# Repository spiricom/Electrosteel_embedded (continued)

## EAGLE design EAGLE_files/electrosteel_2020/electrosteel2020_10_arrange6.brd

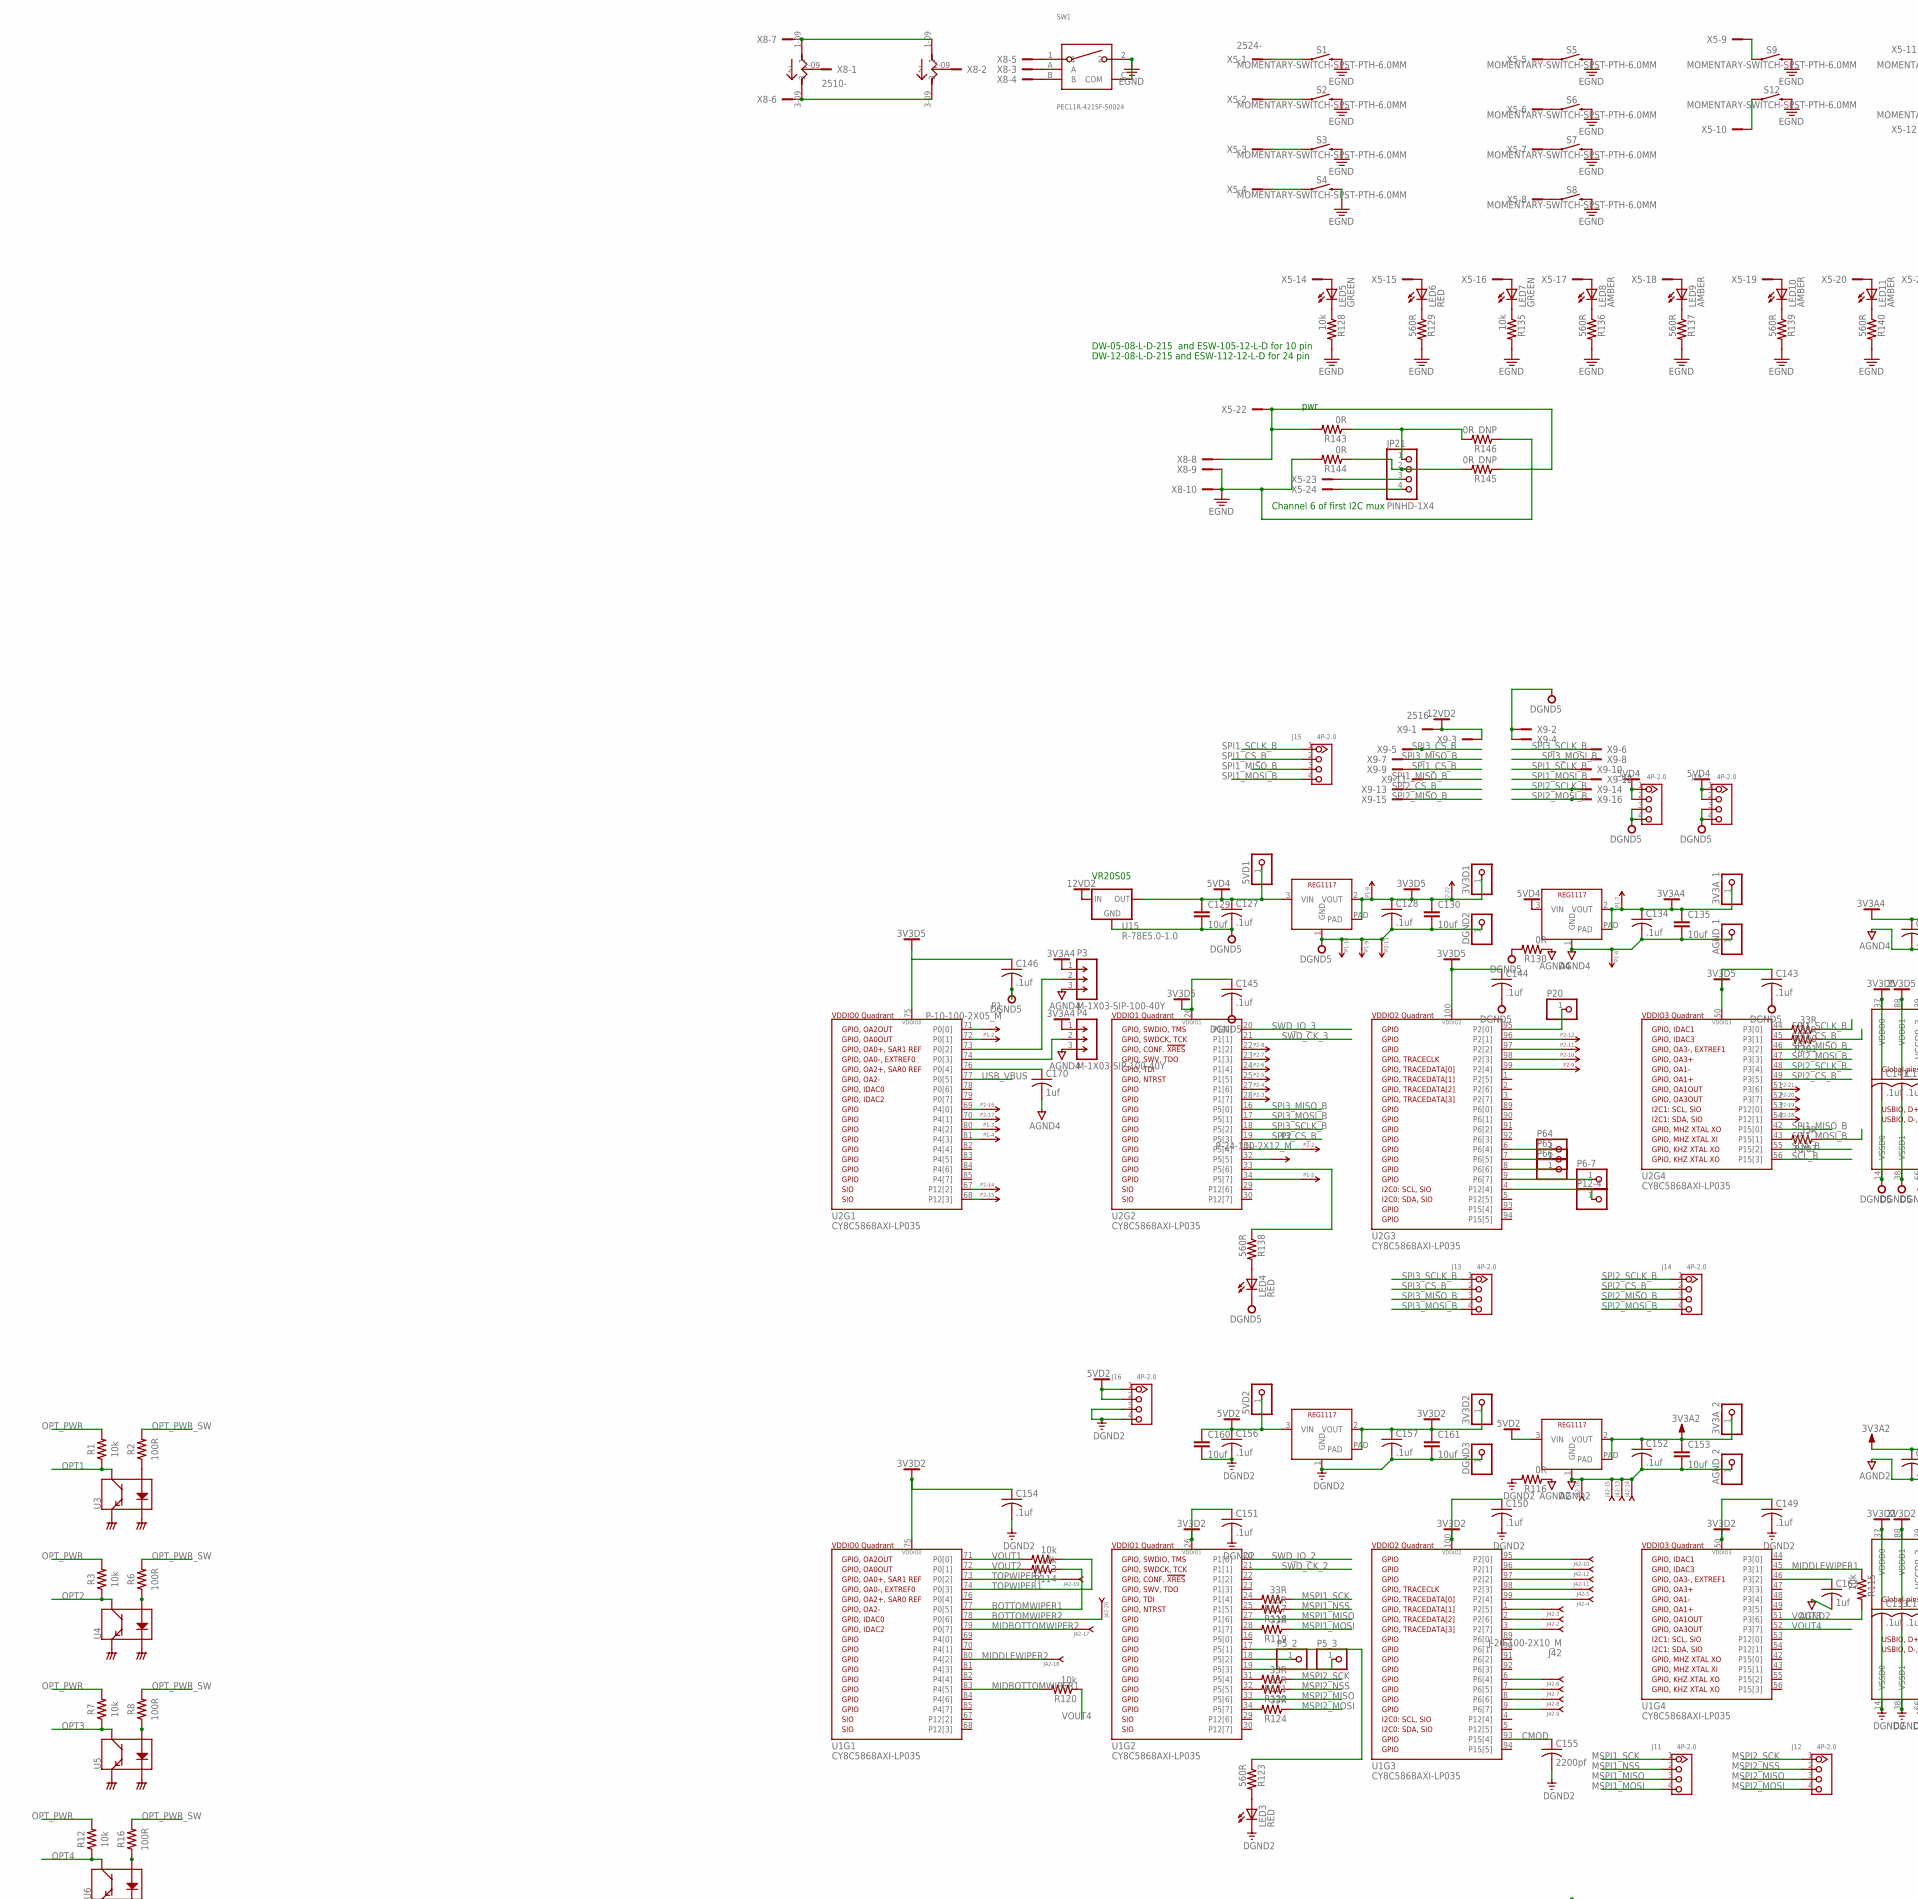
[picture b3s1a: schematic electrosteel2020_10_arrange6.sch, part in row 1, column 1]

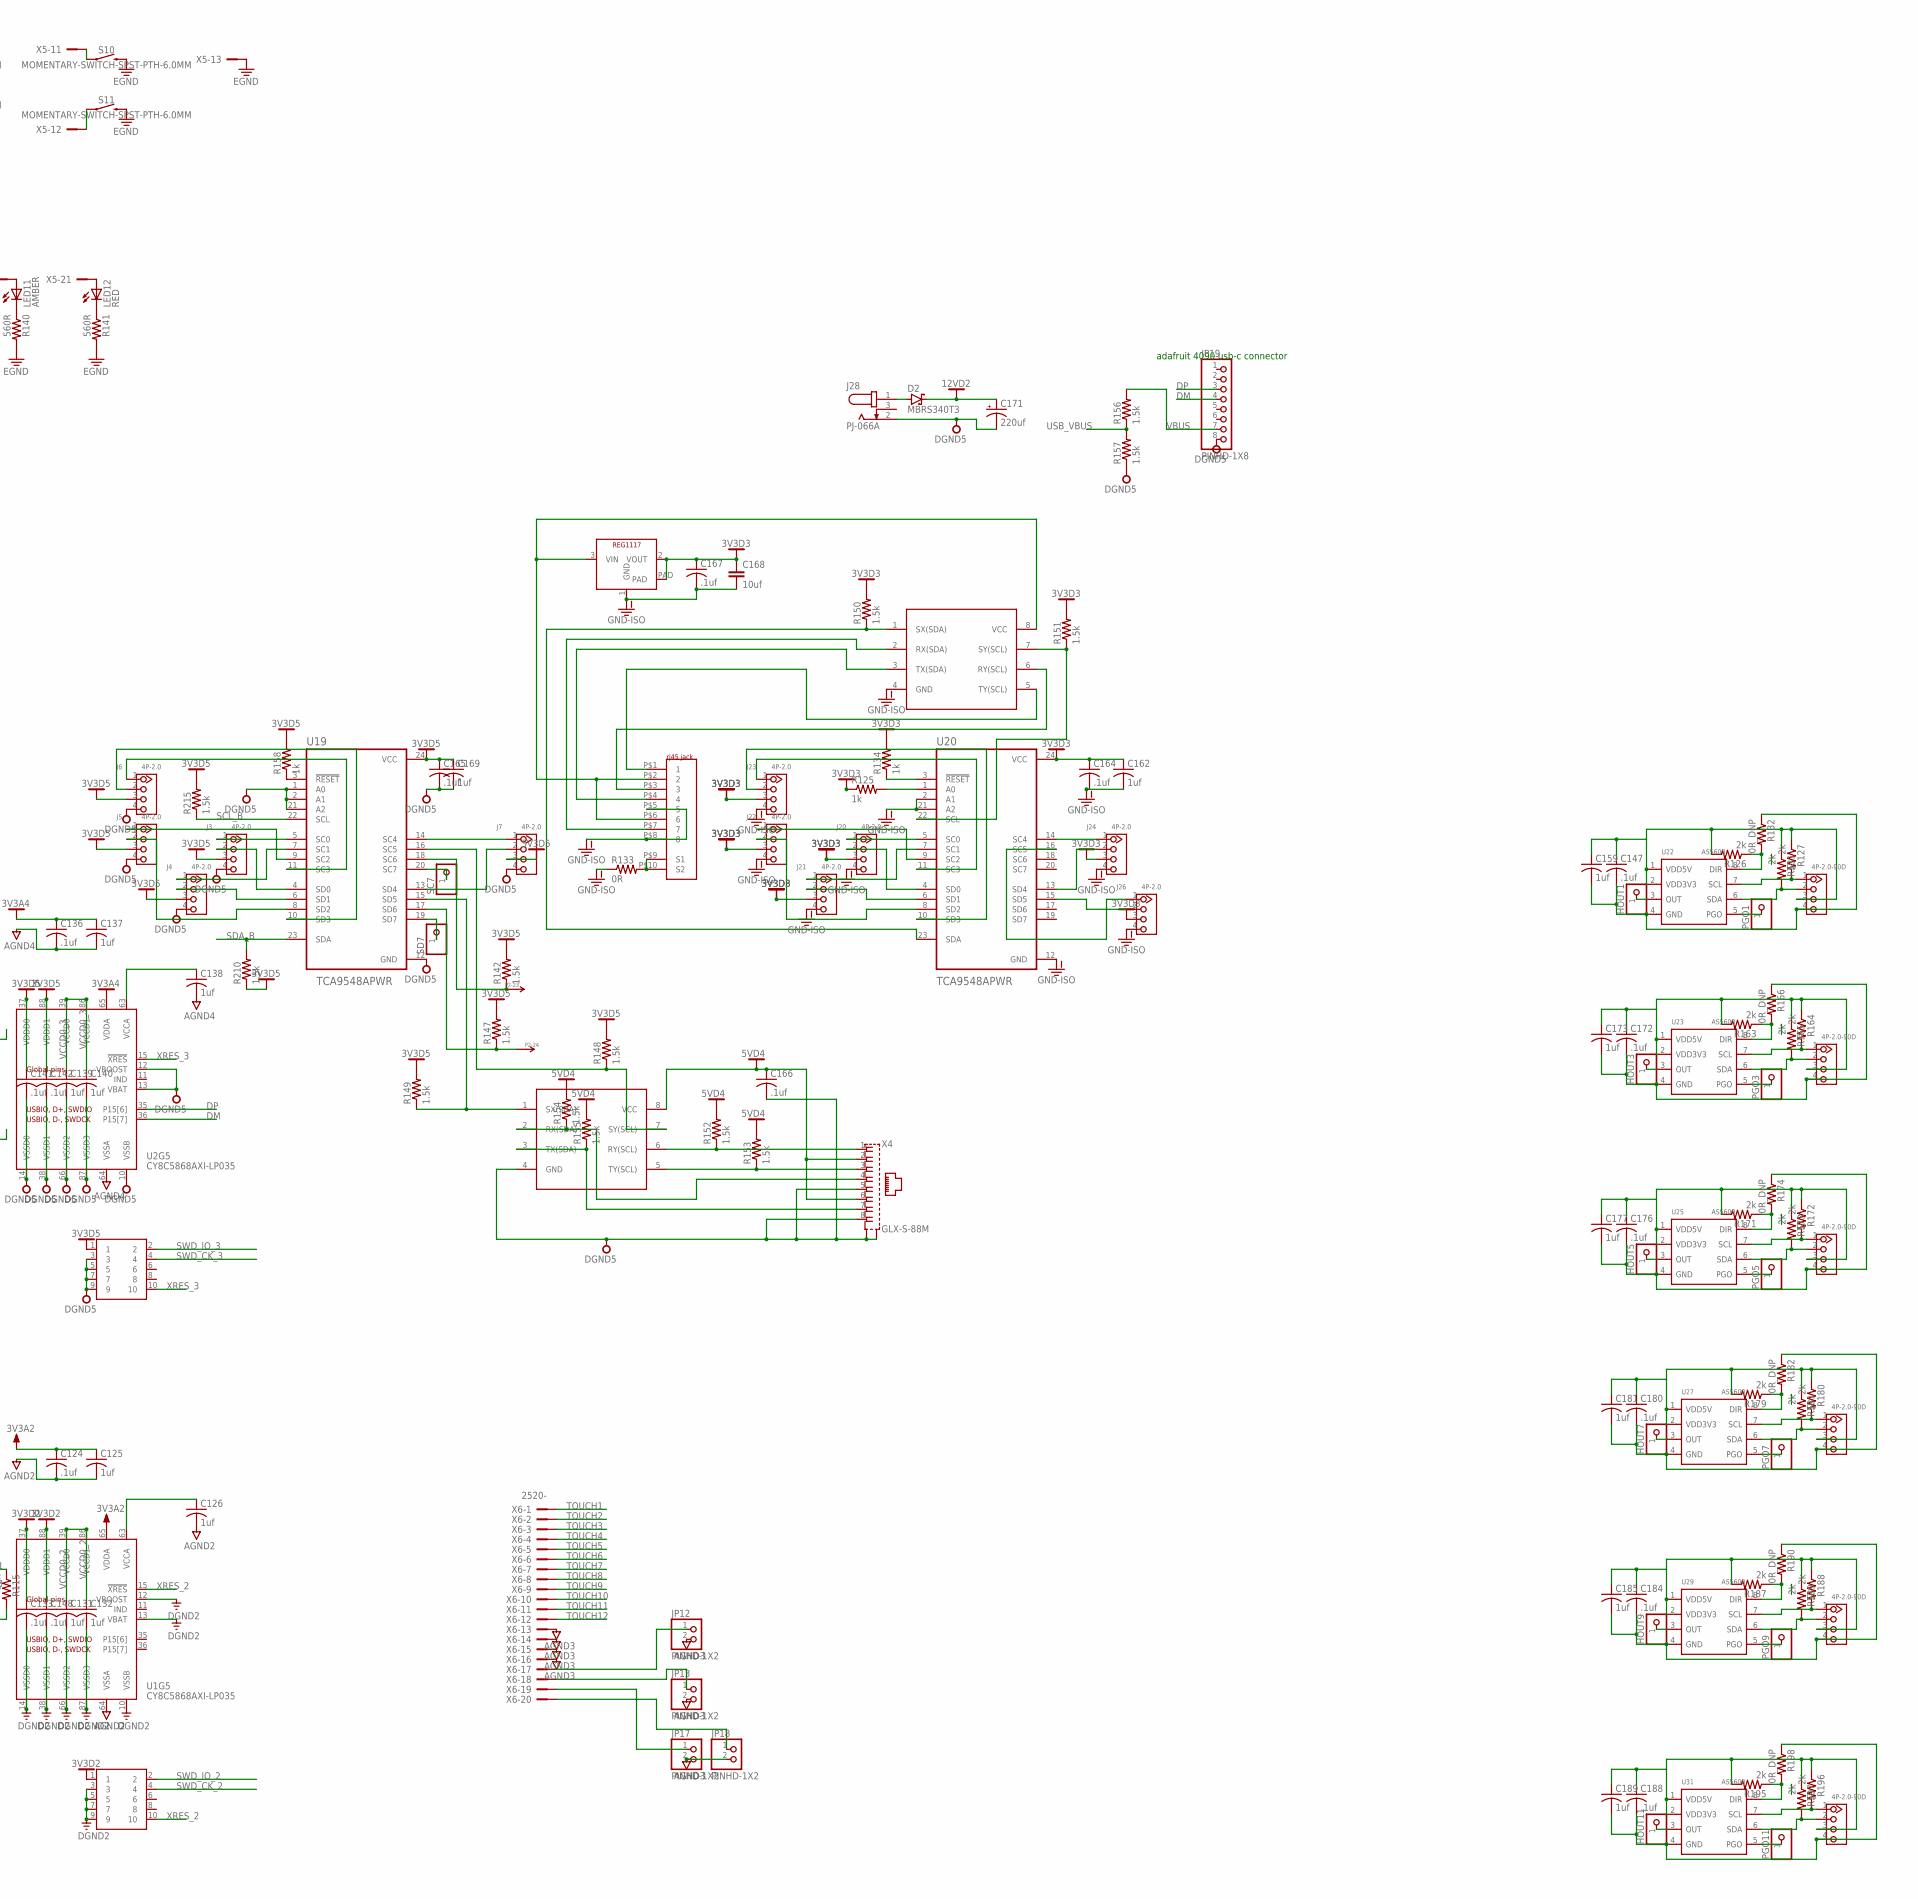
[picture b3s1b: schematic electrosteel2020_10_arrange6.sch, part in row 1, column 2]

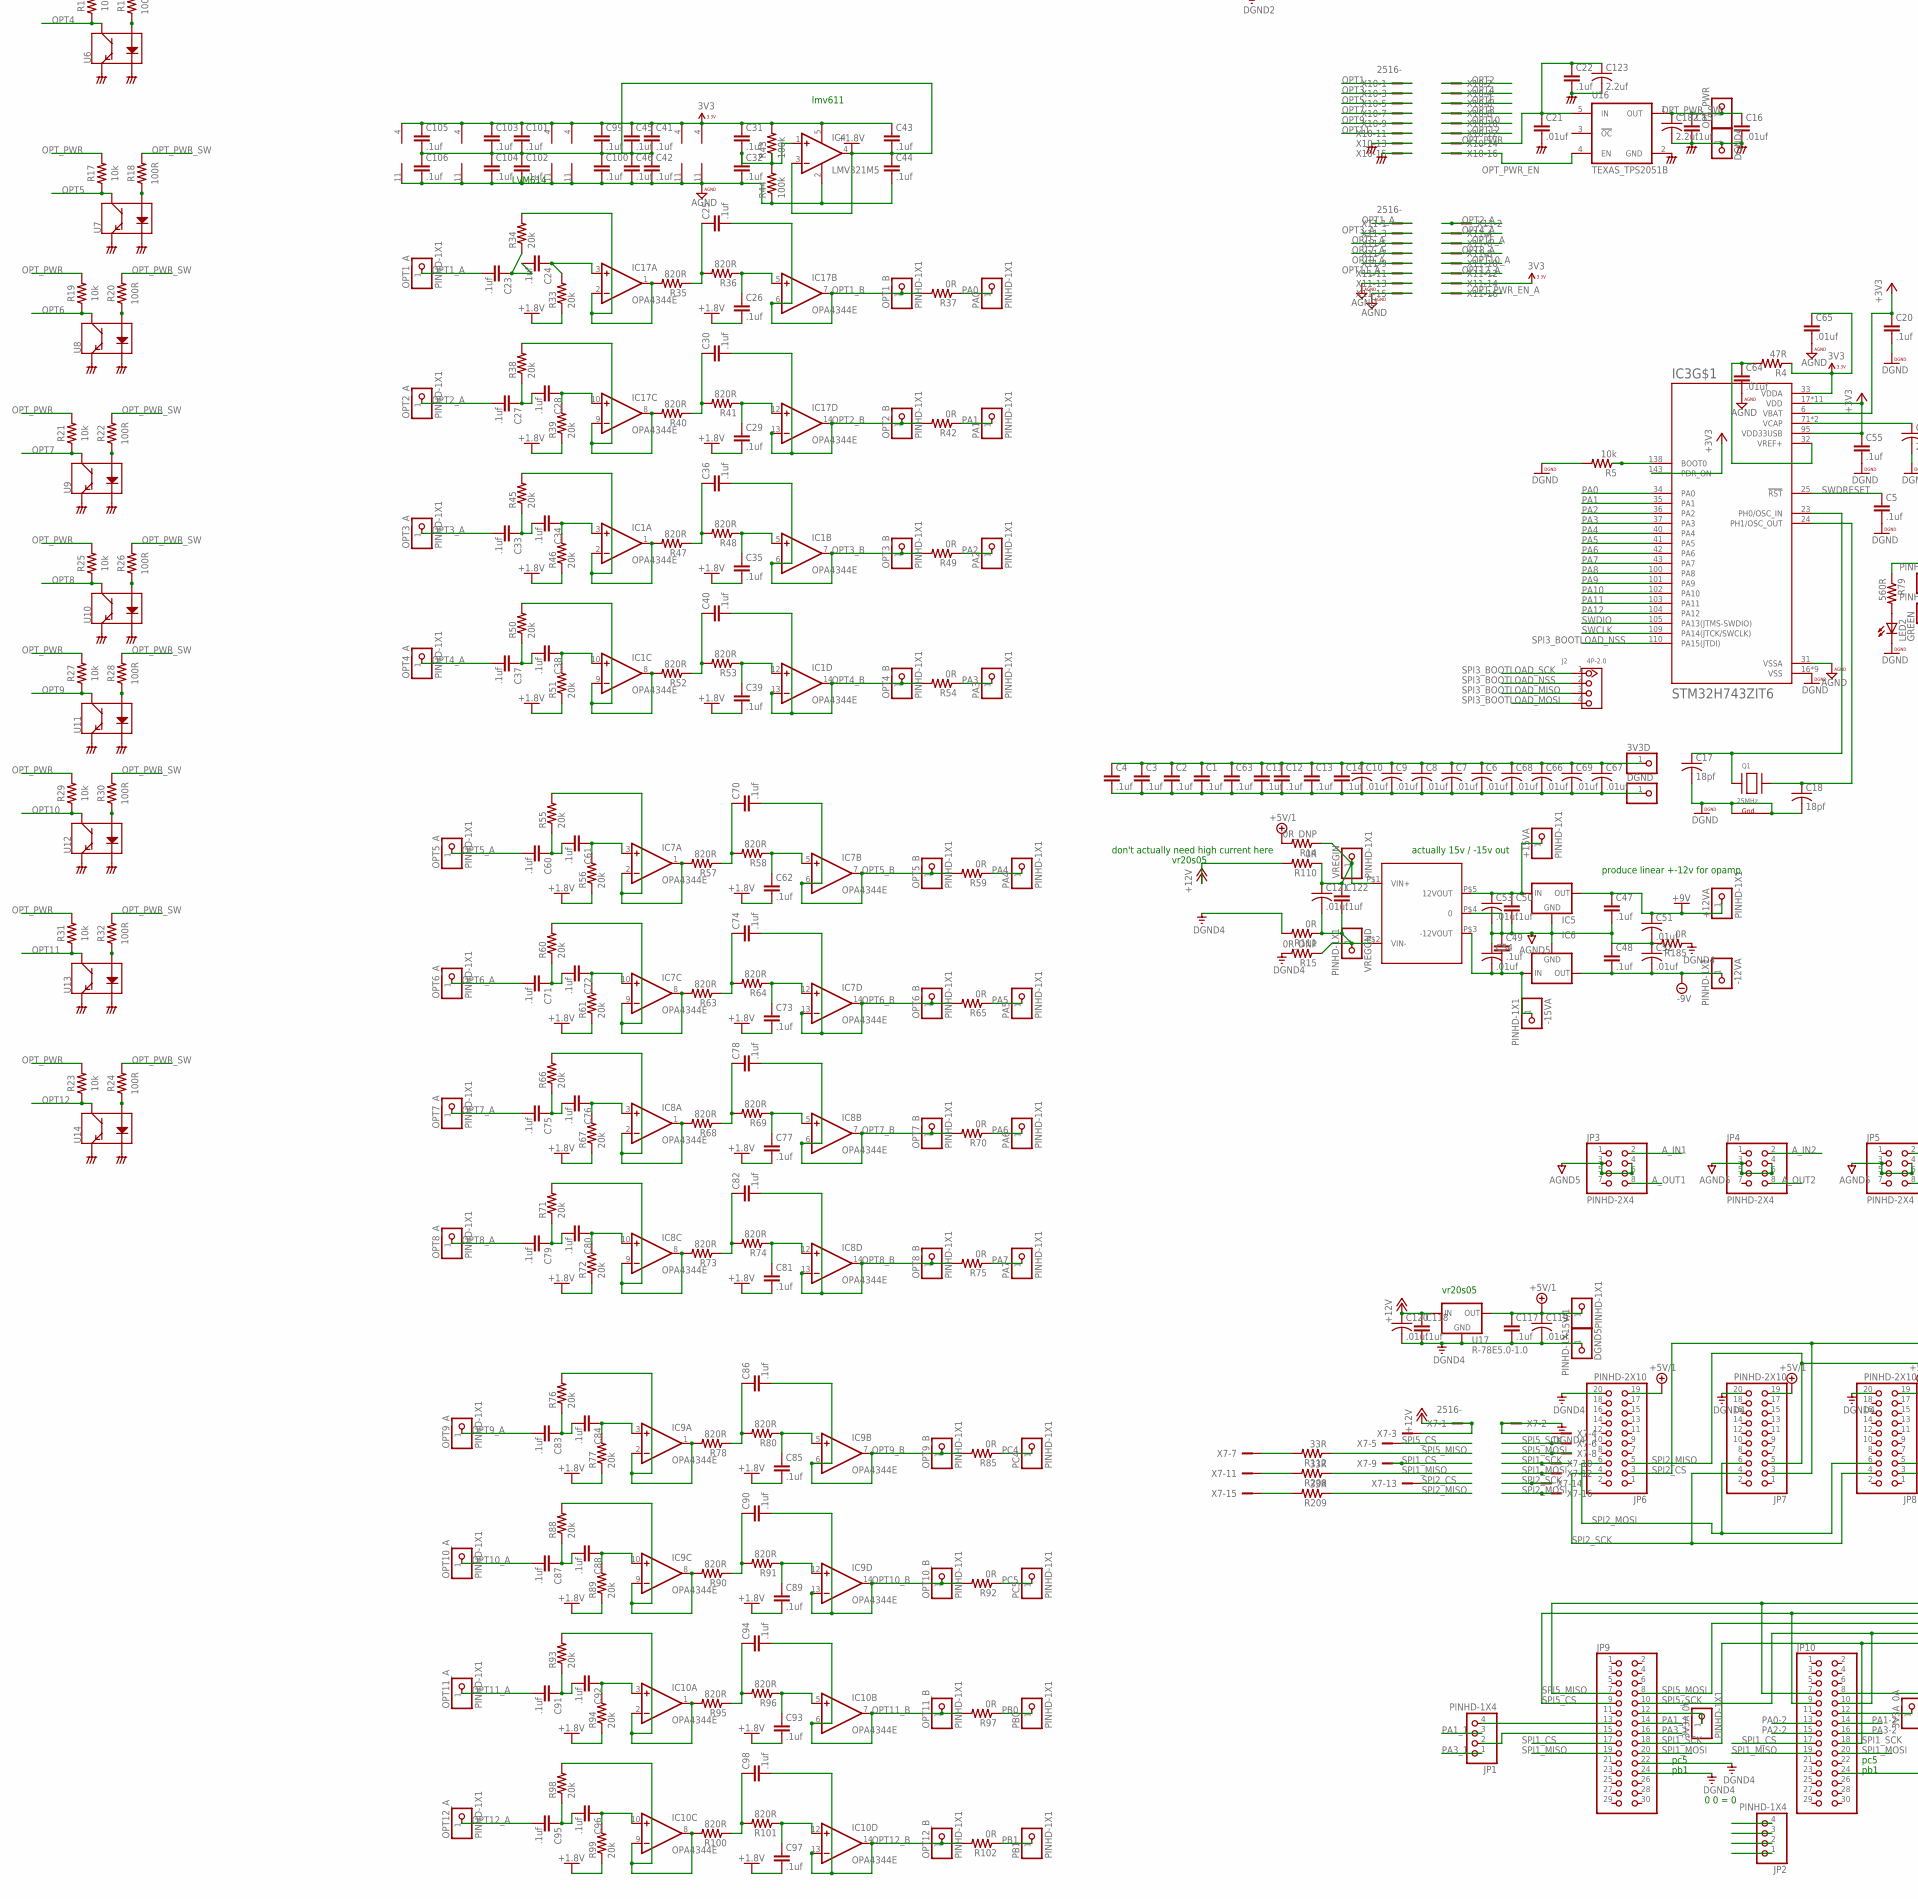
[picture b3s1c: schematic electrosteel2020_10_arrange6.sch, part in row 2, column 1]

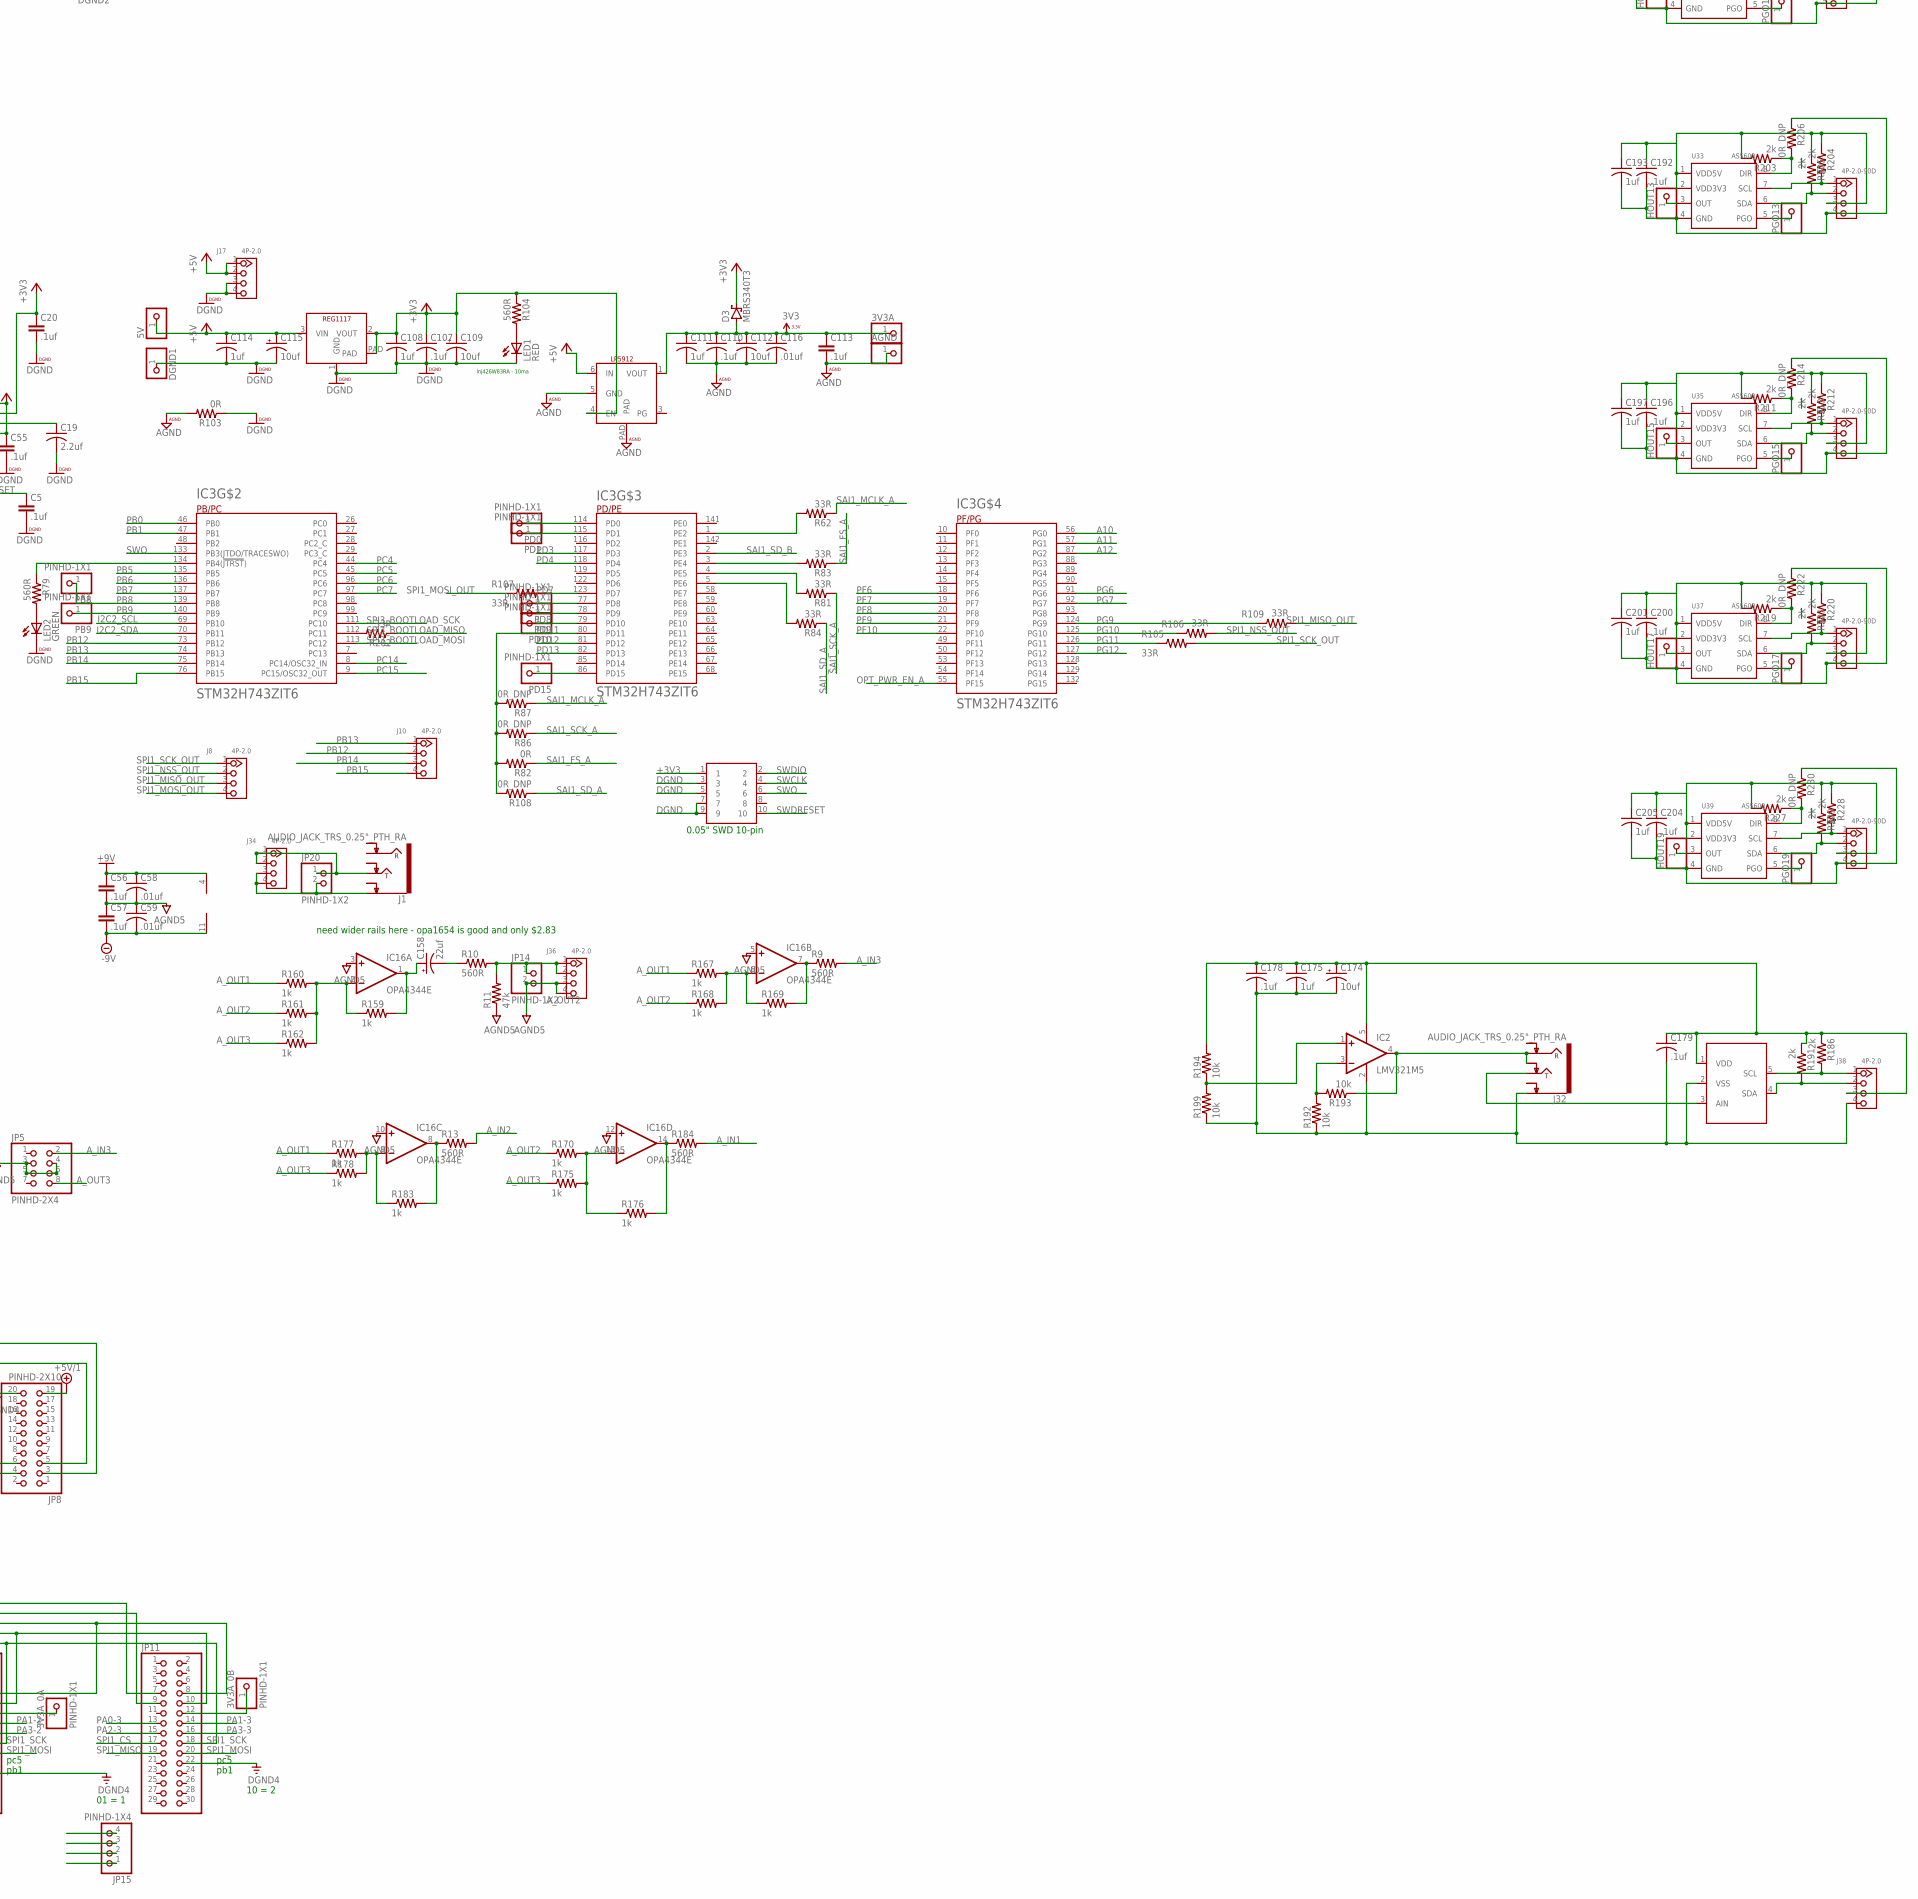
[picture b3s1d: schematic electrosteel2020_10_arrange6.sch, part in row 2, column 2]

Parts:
3V3A, 3V3A_0A, 3V3A_0B, 3V3A_0C, 3V3A_1, 3V3A_2, 3V3D, 3V3D1, 3V3D2, 5V, 5V/1, 5VD1, 5VD2: PINHD-1X1; 1X01; PARTNO *DNP
+12VA, +15VA: PINHD-1X1; 1X01; PARTNO *DNP
-12VA, -15VA: PINHD-1X1; 1X01; PARTNO *DNP
AGND: PINHD-1X1; 1X01; PARTNO *DNP
AGND_1, AGND_2: PINHD-1X1; 1X01; PARTNO *DNP
C1, C2, C3, C4, C5, C11, C12, C13, C14, C15, C20, C22, C23, C24, C25, C26, C27, C28, C29, C30, C31, C32, C33, C34, C35, C36, C37, C38, C39, C40, C41, C42, C43, C44, C45, C46, C47, C48, C49, C50, C55, C56, C57, C60, C61, C62, C63, C70, C71, C72, C73, C74, C75, C76, C77, C78, C79, C80, C81, C82, C83, C84, C85, C86, C87, C88, C89, C90, C91, C92, C93, C94, C95, C96, C97, C98, C99, C100, C101, C102, C103, C104, C105, C106, C113, C117, C118, C122: .1uf; 0402; PARTNO CC0402KRX7R8BB104
C6, C7, C8, C9, C10, C51, C52, C53, C54, C58, C59, C66, C67, C68, C69, C116, C119, C120, C121: .01uf; C0201; PARTNO TMK063B7103KP-F
C16, C21, C64, C65: .01uf; 0402; PARTNO CC0402KRX7R8BB103
C17, C18: 18pf; C0603; PARTNO CL10C180JB8NNNC
C19, C123, C182: 2.2uf; C1206; PARTNO T491A225K020AT
C107, C110, C178, C179: .1uf; C0603; PARTNO CC0603KRX7R8BB104
C108, C111, C114, C175: 1uf; C1206; PARTNO C3216X7R1E105K085AA
C109, C112, C115, C174: 10uf; SMC_B; PARTNO TAJB106K025RNJ
C124, C127, C128, C133, C134, C136, C141, C142, C143, C144, C145, C146, C147, C148, C149, C150, C151, C152, C154, C156, C157, C164, C165, C166, C167, C172, C176, C180, C184, C188, C192, C196, C200, C204: .1uf; C0603K; PARTNO CC0603KRX7R8BB104
C125, C126, C131, C132, C137, C138, C139, C140, C159, C162, C163, C169, C170, C173, C177, C181, C185, C189, C193, C197, C201, C205: 1uf; C1206K; PARTNO C3216X7R1E105K085AA
C129, C130, C135, C153, C160, C161, C168: 10uf; C1206K; PARTNO TMK316F106ZL-T
C155: 2200pf; C0603K; PARTNO C0603C222J5GACTU
C158: 22uf; PANASONIC_D; PARTNO EEE-1CA220NP
C171: 220uf; E5-10,5; PARTNO ESW227M035AH9AA
D2, D3: MBRS340T3; SMC; PARTNO MBRS340T3G
DGND, DGND1, DGND2, DGND3, DGND4, DGND5: PINHD-1X1; 1X01; PARTNO *DNP
HOUT1, HOUT3, HOUT5, HOUT7, HOUT9, HOUT11, HOUT13, HOUT15, HOUT17, HOUT19: PINHD-1X1; 1X01; PARTNO *DNP
IC1, IC7, IC8, IC9, IC10, IC17: OPA4344E; TSSOP14; PARTNO OPA4348AQPWRQ1
IC2: LMV321M5; SOT23-5; PARTNO LMV321M5
IC3: STM32H743ZIT6; QFP50P2200X2200X160-144N; PARTNO STM32H730ZBT6
IC4: LMV321M5; SOT23-5; PARTNO LMV611MF/NOPB
IC5: 78LXX; PARTNO LM78L12ACZ/LFT7
IC6: 79LXX; PARTNO L79L12ACZ-TR
IC11: LP5912; 6-WSON; PARTNO LP5912-3.3DRVT
IC12, IC13, IC14, IC15, IC18, IC20: REG1117; SOT223; PARTNO LD1117S33TR
IC16: OPA4344E; TSSOP14; PARTNO OPA1654AIPWR
J1, J32: AUDIO_JACK_TRS_0.25"_PTH_RA; AUDIO_JACK_0.25"_TRS_PTH_RA; PARTNO NRJ6HM-1
J2, J3, J4, J5, J6, J7, J8, J10, J11, J12, J13, J14, J15, J16, J17, J18, J19, J20, J21, J22, J23, J24, J26, J34, J36, J38: 4P-2.0; HW4-2.0; PARTNO 110990030
J9, J25, J27, J29, J31, J33, J35, J37, J39, J41: 4P-2.0-90D; HW4-2.0-90D; PARTNO 110990037
J28: PJ-066A; CUI_PJ-066A; PARTNO PJ-066A
J42: J-20-100-2X10_M; DIL-100-2X10_M; PARTNO RS2-20-G
JP1, JP2, JP15: PINHD-1X4; 1X04
JP3, JP4, JP5: PINHD-2X4; 2X04; PARTNO 77313-101-08LF
JP6, JP7, JP8: PINHD-2X10; 2X10; PARTNO 77313-101-20LF
JP9, JP10, JP11: PINHD-2X15; 2X15; PARTNO 77313-101-30LF
JP12, JP13, JP14, JP17, JP18, JP20: PINHD-1X2; 1X02; PARTNO *DNP
JP19: PINHD-1X8; 1X08; PARTNO *DNP
JP21: PINHD-1X4; 1X04; PARTNO *DNP
LED1, LED3, LED4: RED; CHIP-LED0603; PARTNO 5973006507F
LED2: GREEN; CHIP-LED0603; PARTNO 5973506507F
LED5, LED7: GREEN; P-LCC-2; PARTNO HSMM-A101-R00J1
LED6, LED12: RED; P-LCC-2; PARTNO HSMZ-A100-R00J1
LED8, LED9, LED10, LED11: AMBER; P-LCC-2; PARTNO HSMU-A100-S00J1
OPT1_A, OPT1_B, OPT2_A, OPT2_B, OPT3_A, OPT3_B, OPT4_A, OPT4_B, OPT5_A, OPT5_B, OPT6_A, OPT6_B, OPT7_A, OPT7_B, OPT8_A, OPT8_B, OPT9_A, OPT9_B, OPT10_A, OPT10_B, OPT11_A, OPT11_B, OPT12_A, OPT12_B: PINHD-1X1; 1X01; PARTNO *DNP
OPT_PWR: PINHD-1X1; 1X01; PARTNO *DNP
P1: P-10-100-2X05_M; DIL-100-2X05_M; PARTNO ESW-105-12-L-D
P2: P-24-100-2X12_M; DIL-100-2X12_M; PARTNO ESW-112-12-L-D
P3, P4: M-1X03-SIP-100-40Y; SIP-100-03-40Y; PARTNO *DNP
P5_2, P5_3, P6-7, P12-4, P20, P64, P65, P66: PINHD-1X1; 1X01; PARTNO *DNP
PA0, PA1, PA2, PA3, PA4, PA5, PA6, PA7: PINHD-1X1; 1X01; PARTNO *DNP
PB0, PB1, PB8, PB9: PINHD-1X1; 1X01; PARTNO *DNP
PC4, PC5: PINHD-1X1; 1X01; PARTNO *DNP
PD0, PD1, PD8, PD9, PD10, PD15: PINHD-1X1; 1X01; PARTNO *DNP
PGO1, PGO3, PGO5, PGO7, PGO9, PGO11, PGO13, PGO15, PGO17, PGO19: PINHD-1X1; 1X01; PARTNO *DNP
Q1: 25MHz; NX3225; PARTNO 7M-25.000MAAJ-T
R1, R3, R7, R12, R17, R19, R21, R23, R25, R27, R29, R31: 10k; RESC1608X60; PARTNO ESR03EZPF1002
R2, R6, R8, R16, R18, R20, R22, R24, R26, R28, R30, R32: 100R; RESC1608X60; PARTNO ESR03EZPJ101
R4: 47R; R0603; PARTNO ESR03EZPJ470
R5: 10k; R0603; PARTNO RC0402FR-0710KL
R9, R10, R13, R79, R104, R123, R129, R136, R137, R138, R139, R140, R141, R184: 560R; R0603; PARTNO ESR03EZPF5600
R11: 47k; R0603; PARTNO ESR03EZPJ473
R14, R15, R86, R87, R108, R132, R145, R146, R166, R174, R182, R190, R198, R206, R214, R222, R230: 0R_DNP; R0603; PARTNO *DNP
R33, R34, R38, R39, R45, R46, R50, R51, R55, R56, R60, R61, R66, R67, R71, R72, R76, R77, R88, R89, R93, R94, R98, R99: 20k; R0603; PARTNO ESR03EZPF2002
R35, R36, R40, R41, R47, R48, R52, R53, R57, R58, R63, R64, R68, R69, R73, R74, R78, R80, R90, R91, R95, R96, R100, R101: 820R; R0603; PARTNO RCS0603820RFKEA
R37, R42, R49, R54, R59, R65, R70, R75, R85, R92, R97, R102, R133: 0R; R0603; PARTNO RC0603JR-070RL
R43, R44: 100k; R0603; PARTNO ESR03EZPF1003
R62, R81, R83, R84, R112, R117, R118, R119, R121, R122, R124, R200, R201, R202, R207, R208, R209: 33R; R0201; PARTNO RC0201FR-0733RL
R82, R103, R110, R111, R185: 0R; R0603; PARTNO RCS06030000Z0EA
R105, R106, R107, R109: 33R; 0402; PARTNO RC0402FR-0733RL
R113, R114, R115, R120, R192, R193, R194, R199: 10k; R0603; PARTNO ESR03EZPF1002
R116, R130, R143, R144: 0R; R0603; PARTNO CRCW06030000Z0EAHP
R125, R134, R158, R159, R160, R161, R162, R167, R168, R169, R170, R175, R176, R177, R178, R183: 1k; R0603; PARTNO ESR03EZPF1001
R126, R127, R131, R163, R164, R165, R171, R172, R173, R179, R180, R181, R186, R187, R188, R189, R191, R195, R196, R197, R203, R204, R205, R211, R212, R213, R219, R220, R221, R227, R228, R229: 2k; R0603; PARTNO ERJ-PA3F2001V
R128, R135: 10k; R0603; PARTNO ESR03EZPF5600
R142, R147, R148, R149, R150, R151, R152, R153, R154, R155, R156, R157, R210, R215: 1.5k; R0603; PARTNO ESR03EZPJ152
S1, S2, S3, S4, S5, S6, S7, S8, S9, S10, S11, S12: MOMENTARY-SWITCH-SPST-PTH-6.0MM; TACTILE_SWITCH_PTH_6.0MM; PARTNO TL1105SPF160Q
SC7: PINHD-1X1; 1X01; PARTNO *DNP
SD7: PINHD-1X1; 1X01; PARTNO *DNP
SW1: PEC11R-4215F-S0024; PARTNO PEC11R-4215F-S0024
U1: CY8C5868AXI-LP035; TQFP-100-14X14MM; PARTNO CY8C5888AXI-LP096
U2: CY8C5868AXI-LP035; TQFP-100-14X14MM; PARTNO CY8C5468AXI-LP042
U3, U4, U5, U6, U7, U8, U9, U10, U11, U12, U13, U14: QRE1113; PARTNO QRE1113GR
U15, U17: R-78E5.0-1.0; DC-DC_CONVERTER_78XX; PARTNO R-78E5.0-1.0
U16: TEXAS_TPS2051B; TEXAS_SOT23-5; PARTNO TPS2051BDBVRG4
U19, U20: TCA9548APWR; SOP65P640X120-24N; PARTNO TCA9548APWR
U22, U23, U25, U27, U29, U31, U33, U35, U37, U39: AS5600; SOIC8-1.27-5X4MM; PARTNO AS5600-ASOM
U$1, U$2: RK09; PARTNO RK09L1220A1B
U$3: CMR0512S3C; PARTNO DPU01M-15
U$5: MCP3221; SOT23-5L; PARTNO MCP3221A7T-E/OT
U$6: SS-7188VS-A-FLS; SS-7188VS-A-FLS_RJ45; PARTNO SS-7188VS-A-FLS
U$9, U$10: P82B96DP,118; SO8; PARTNO P82B96TD*112
VREGGND: PINHD-1X1; 1X01; PARTNO *DNP
VREGIN: PINHD-1X1; 1X01; PARTNO *DNP
X1, X2, X3: 3221-10-0300-00; PARTNO 4048
X4: GLX-S-88M; PARTNO GLX-S-88M
X5: 2524-; PAK100/2500-24; PARTNO DW-12-08-L-D-215
X6: 2520-; PAK100/2500-20; PARTNO N2520-6003-UG
X7, X9, X10, X11: 2516-; PAK100/2500-16; PARTNO D2516-6002-AR
X8: 2510-; PAK100/2500-10; PARTNO DW-05-08-L-D-215

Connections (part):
3V3: C31.1, C41.1, C43.1, C45.1, C99.1, C101.1, C103.1, C105.1, IC1.4 (V+), IC4.5 (V+), IC7.4 (V+), IC8.4 (V+), IC9.4 (V+), IC10.4 (V+), IC17.4 (V+), R43.2, X11.14
3V3A: 3V3A.1, C65.1, C110.1, C111.1, C112.+, C113.1, C116.1, D3.A, IC3.33 (VDDA), IC11.1 (VOUT), R4.1
3V3A2: 3V3A_2.1, C124.1, C125.1, C152.1, C153.1, IC18.2 (VOUT), IC18.PAD, U1.65 (VDDA)
3V3A4: 3V3A_1.1, C134.1, C135.1, C136.1, C137.1, IC14.2 (VOUT), IC14.PAD, P1.7, P3.1, P4.1, U2.65 (VDDA)
3V3D2: 3V3D2.1, C133.1, C148.1, C149.1, C150.1, C151.1, C154.1, C157.1, C161.1, IC20.2 (VOUT), IC20.PAD, U1.26 (VDDIO1), U1.37 (VDDD0), U1.50 (VDDIO3), U1.75 (VDDIO0), U1.88 (VDDD1), U1.100 (VDDIO2), X3.1
3V3D3: C162.1, C164.1, C167.1, C168.1, IC15.2 (VOUT), IC15.PAD, J20.3, J21.3, J22.3, J23.3, J24.3, J26.3, R125.1, R134.2, R150.2, R151.2, U20.24 (VCC)
3V3D5: 3V3D1.1, C128.1, C130.1, C141.1, C142.1, C143.1, C144.1, C145.1, C146.1, C165.1, C169.1, IC13.2 (VOUT), IC13.PAD, J3.3, J4.3, J5.3, J6.3, J7.3, P1.8, P2.22, R142.2, R147.2, R148.2, R149.2, R158.2, R210.1, R215.2, U2.26 (VDDIO1), U2.37 (VDDD0), U2.50 (VDDIO3), U2.75 (VDDIO0), U2.88 (VDDD1), U2.100 (VDDIO2), U19.24 (VCC), X1.1
5VD2: 5VD2.1, C156.1, C160.1, IC18.3 (VIN), IC20.3 (VIN), J16.1, J16.2
5VD4: 5VD1.1, C127.1, C129.1, C166.1, IC13.3 (VIN), IC14.3 (VIN), J18.1, J18.2, J19.1, J19.2, R152.2, R153.2, R154.2, R155.2, U15.VOUT (OUT), U$9.8 (VCC), X4.2, X4.6
12VD2: C171.+, D2.C, U15.VIN (IN), X9.1, X9.3
+1.8V: C26.2, C29.2, C35.2, C39.2, C41.2, C42.1, C43.2, C44.1, C45.2, C46.1, C62.2, C73.2, C77.2, C81.2, C85.2, C89.2, C93.2, C97.2, C99.2, C100.1, C101.2, C102.1, C103.2, C104.1, C105.2, C106.1, IC4.3 (-IN), IC4.4 (OUT), R33.1, R39.1, R46.1, R51.1, R56.1, R61.1, R67.1, R72.1, R77.1, R89.1, R94.1, R99.1
+3V3: 3V3D.1, C1.1, C2.1, C3.1, C4.1, C6.1, C7.1, C8.1, C9.1, C10.1, C11.1, C12.1, C13.1, C14.1, C20.1, C55.1, C63.1, C66.1, C67.1, C68.1, C69.1, C107.1, C108.1, C109.+, D3.C, IC3.6 (VBAT), IC3.17 (VDD), IC3.30 (VDD), IC3.39 (VDD), IC3.52 (VDD), IC3.62 (VDD), IC3.72 (VDD), IC3.84 (VDD), IC3.95 (VDD33USB), IC3.108 (VDD), IC3.121 (VDD), IC3.131 (VDD), IC3.143 (PDR_ON), IC3.144 (VDD), IC11.4 (EN), IC12.2 (VOUT), IC12.PAD, R104.1, X2.1
+5V: 5V.1, C114.1, C115.+, IC11.6 (IN), IC12.3 (VIN), J17.1, J17.2
+5V/1: 5V/1.1, C117.1, C119.1, JP6.19, JP7.19, JP8.19, R14.2, U17.VOUT (OUT)
+9V: +12VA.1, C47.1, C51.1, C56.1, C58.1, IC5.OUT, IC16.4 (V+)
+12V: C118.1, C120.1, R110.2, U17.VIN (IN), X7.1, X7.3
-9V: -12VA.1, C48.2, C52.2, C57.2, C59.2, IC6.OUT, IC16.11 (V-)
A10: IC3.56 (PG0)
A11: IC3.57 (PG1)
A12: IC3.87 (PG2)
AGND: AGND.1, C32.2, C42.2, C44.2, C46.2, C64.2, C65.2, C100.2, C102.2, C104.2, C106.2, C110.2, C111.2, C112.-, C113.2, C116.2, IC1.11 (V-), IC3.31 (VSSA), IC4.2 (V-), IC7.11 (V-), IC8.11 (V-), IC9.11 (V-), IC10.11 (V-), IC11.5 (GND), IC11.PAD, IC17.11 (V-), R44.1, R103.2, X11.13, X11.15
AGND2: AGND_2.1, C124.2, C125.2, C126.2, C152.2, C153.2, C163.2, IC18.1 (GND), J42.13, J42.14, J42.15, J42.16, R116.1, U1.64 (VSSA)
AGND3: JP12.2, JP13.2, JP17.2, JP18.2, X6.13, X6.14, X6.15, X6.16
AGND4: AGND_1.1, C134.2, C135.2, C136.2, C137.2, C138.2, C170.2, IC14.1 (GND), P1.6, P3.3, P4.3, R130.1, U2.64 (VSSA)
AGND5: C47.2, C48.1, C49.1, C50.2, C51.2, C52.1, C53.2, C54.1, C56.2, C57.1, C58.2, C59.1, IC5.GND, IC6.GND, IC16.3 (+IN), IC16.5 (+IN), IC16.10 (+IN), IC16.12 (+IN), J36.3, J36.4, JP3.3, JP3.4, JP3.5, JP3.6, JP4.3, JP4.4, JP4.5, JP4.6, JP5.3, JP5.4, JP5.5, JP5.6, JP14.2, R11.1, R185.2, U$3.P$4 (0)
A_IN1: JP3.2, R184.2
A_IN2: JP4.2, R13.2
A_IN3: JP5.2, R9.2
A_OUT1: JP3.8, R160.1, R167.1, R177.1
A_OUT2: JP4.8, R161.1, R168.1, R170.1
A_OUT3: JP5.8, R162.1, R175.1, R178.1
BOTTOMWIPER1: R114.1, U1.77 (P0[5])
BOTTOMWIPER2: J42.20, U1.78 (P0[6])
CGND: C15.2, C16.2, C21.2, C22.2, C123.2, C182.2, DGND4.1, U3.2 (K), U3.4 (E), U4.2 (K), U4.4 (E), U5.2 (K), U5.4 (E), U6.2 (K), U6.4 (E), U7.2 (K), U7.4 (E), U8.2 (K), U8.4 (E), U9.2 (K), U9.4 (E), U10.2 (K), U10.4 (E), U11.2 (K), U11.4 (E), U12.2 (K), U12.4 (E), U13.2 (K), U13.4 (E), U14.2 (K), U14.4 (E), U16.2 (GND), X10.13, X10.15
CMOD: C155.1, U1.93 (P15[4])
DGND: C1.2, C2.2, C3.2, C4.2, C5.2, C6.2, C7.2, C8.2, C9.2, C10.2, C11.2, C12.2, C13.2, C14.2, C17.2, C18.2, C19.2, C20.2, C55.2, C63.2, C66.2, C67.2, C68.2, C69.2, C107.2, C108.2, C109.-, C114.2, C115.-, DGND.1, DGND1.1, IC3.16 (VSS), IC3.38 (VSS), IC3.51 (VSS), IC3.61 (VSS), IC3.83 (VSS), IC3.94 (VSS), IC3.107 (VSS), IC3.120 (VSS), IC3.130 (VSS), IC12.1 (GND), J17.3, J17.4, LED1.C, LED2.C, Q1.2 (G2), Q1.4 (G1), R5.2, R103.1, X2.3, X2.5, X2.7, X2.9
DGND2: C131.2, C132.2, C133.2, C148.2, C149.2, C150.2, C151.2, C154.2, C155.2, C156.2, C157.2, C160.2, C161.2, DGND3.1, IC20.1 (GND), J16.3, J16.4, LED3.C, R116.2, U1.10 (VSSB), U1.12 (VBOOST), U1.13 (VBAT), U1.14 (VSSD0), U1.38 (VSSD1), U1.66 (VSSD2), U1.87 (VSSD3), X3.3, X3.5, X3.7, X3.9
DGND4: C117.2, C118.2, C119.2, C120.2, DGND5.1, JP6.20, JP7.20, JP8.20, JP9.22, JP9.24, JP10.24, JP11.22, R15.2, R111.2, R185.1, U17.GND, X7.2, X7.4
DGND5: C127.2, C128.2, C129.2, C130.2, C139.2, C140.2, C141.2, C142.2, C143.2, C144.2, C145.2, C146.2, C165.2, C166.2, C169.2, C171.-, DGND2.1, IC13.1 (GND), J3.4, J4.4, J5.4, J6.4, J7.4, J18.3, J18.4, J19.3, J19.4, J28.2, JP19.8, LED4.C, P1.9, P1.10, P2.13, R130.2, R157.1, U2.10 (VSSB), U2.12 (VBOOST), U2.13 (VBAT), U2.14 (VSSD0), U2.38 (VSSD1), U2.66 (VSSD2), U2.87 (VSSD3), U15.GND, U19.1 (A0), U19.2 (A1), U19.12 (GND), U19.21 (A2), U$9.4 (GND), X1.3, X1.5, X1.7, X1.9, X4.5, X4.8, X4.S1, X4.S2, X9.2, X9.4
DM: JP19.4, U2.36 (P15[7])
DP: JP19.3, U2.35 (P15[6])
EGND: R128.2, R129.2, R135.2, R136.2, R137.2, R139.2, R140.2, R141.2, R144.2, R146.1, S1.3 (2), S2.3 (2), S3.3 (2), S4.3 (2), S5.3 (2), S6.3 (2), S7.3 (2), S8.3 (2), S9.3 (2), S10.3 (2), S11.3 (2), S12.3 (2), SW1.2, SW1.C (COM), X5.13, X8.9, X8.10
GND-ISO: C162.2, C164.2, C167.2, C168.2, IC15.1 (GND), J20.4, J21.4, J22.4, J23.4, J24.4, J26.4, R133.1, U20.2 (A1), U20.12 (GND), U20.21 (A2), U$6.P$5 (5), U$6.P$8 (8), U$10.4 (GND)
I2C2_SCL: IC3.69 (PB10)
I2C2_SDA: IC3.70 (PB11)
MIDBOTTOMWIPER1: R120.2, U1.83 (P4[5])
MIDBOTTOMWIPER2: J42.17, U1.79 (P0[7])
MIDDLEWIPER1: R115.1, U1.45 (P3[1])
MIDDLEWIPER2: J42.18, U1.80 (P4[2])
MSPI1_MISO: J11.3, U1.27 (P1[6])
MSPI1_MOSI: J11.4, R119.1
MSPI1_NSS: J11.2, R118.1
MSPI1_SCK: J11.1, R117.1
MSPI2_MISO: J12.3, U1.33 (P5[6])
MSPI2_MOSI: J12.4, R124.1
MSPI2_NSS: J12.2, R122.1
MSPI2_SCK: J12.1, R121.1
unnamed: R6.1, U4.1 (A)
unnamed: R2.1, U3.1 (A)
unnamed: IC3.77 (PD8), PD8.1
unnamed: IC3.78 (PD9), PD9.1
unnamed: LED2.A, R79.2
unnamed: IC3.134 (PB4(!JTRST!)), R79.1
unnamed: R8.1, U5.1 (A)
unnamed: IC3.4 (PE5), R81.2
unnamed: J42.1, U1.3 (P2[7])
unnamed: IC16.6 (-IN), R167.2, R168.2, R169.1
unnamed: JP17.1, X6.19
unnamed: JP18.1, X6.20
unnamed: IC3.3 (PE4), R83.2
unnamed: JP13.1, X6.18
unnamed: JP12.1, X6.17
unnamed: LED3.A, R123.2
unnamed: IC3.5 (PE6), R84.2
unnamed: R123.1, U1.17 (P5[1])
unnamed: IC3.1 (PE2), R62.2
unnamed: P5_2.1, U1.18 (P5[2])
unnamed: P5_3.1, U1.19 (P5[3])
unnamed: C138.1, U2.63 (VCCA)
unnamed: C170.1, U2.76 (P0[4])
unnamed: J42.2, U1.2 (P2[6])
unnamed: J42.3, U1.1 (P2[5])
unnamed: D2.A, J28.1
unnamed: IC16.2 (-IN), R159.1, R160.2, R161.2, R162.2
unnamed: IC16.7 (OUT), R9.1, R169.2
unnamed: IC16.9 (-IN), R177.2, R178.2, R183.1
unnamed: +15VA.1, C50.1, C53.1, IC5.IN, U$3.P$5 (12VOUT)
unnamed: C60.1, C61.2, R55.1
unnamed: C158.+, IC16.1 (OUT), R159.2
unnamed: R16.1, U6.1 (A)
unnamed: -15VA.1, C49.2, C54.2, IC6.IN, U$3.P$3 (-12VOUT)
unnamed: R18.1, U7.1 (A)
unnamed: R20.1, U8.1 (A)
unnamed: R22.1, U9.1 (A)
unnamed: R24.1, U14.1 (A)
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
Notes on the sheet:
0.05" SWD 10-pin
produce linear +-12v for opamp
VR20S05
LVM614
lmv611
lnj426W83RA - 10ma
vr20s05
0 0 = 0
01 = 1
10 = 2
don't actually need high current here
adafruit 4090 usb-c connector
pwr
pc5
pb1
DW-05-08-L-D-215 and ESW-105-12-L-D for 10 pin
DW-12-08-L-D-215 and ESW-112-12-L-D for 24 pin
need wider rails here - opa1654 is good and only $2.83
actually 15v / -15v out
Channel 6 of first I2C mux
